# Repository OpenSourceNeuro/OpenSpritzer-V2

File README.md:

<h1 align="center"> OpenSpritzer v2</h1>
<h3 align="center">  An Open hardware pressure ejection system for reliably delivering picolitre volumes.</h3></p>
<h6 align="right">developed by M.J.Y. Zimmermann</h6>

<br></br>

This project is licensed under the <a href="https://www.gnu.org/licenses/gpl-3.0.html">GNU General Public License v3.0</a>
<br>
The hardware is licensed under the <a href="https://cern-ohl.web.cern.ch">CERN OHL v1.2</a>

***

<div align= "justify">

<p>
Designed for ease of use, robustness and low-cost, the “Openspritzer” is an open hardware “Picospritzer” as routinely used in biological labs around the world. The performance of Openspritzer and commercial alternatives is effectively indistiguishable.
</p>

<p>
The system is based on a solenoid valve connected to a pressure gauge. Control can be attained directly via an external TTL pulse or internally through an Arduino set by a rotary encoder. The basic setup can be put together for ~400€, or substantially less if you are prepare to shop around.
</p>

<p>
We anticipate that due to its high performance and low cost Openspritzer will be of interest to a broad range of researchers working in the life and physical sciences.
</p>

<br>

</div>

<p align= "right">
The original work was published in <a href="https://www.nature.com/articles/s41598-017-02301-2"> Forman et al. 2017, Scientific Reports</a>
</p>

***

<h2 align="left">
OpenSpritzer, a DIY open source micro-injector:
</h2>

<br>

<div align= "justify">

<p>
Compared to similar commercial systems that can cost up to several thousand pounds, the cost of the fully equipped Openspritzer (~£300) makes it particularly attractive for those wishing to pursue cutting-edge techniques in low resource environments.
</p>

<p>
This repository contains detailed <a href="https://github.com/OpenSourceNeuro/OpenSpritzer-V2/blob/main/Installation_Manual.md">assembly instructions and an operation manual</a> for OpenSpritzer. The <a href="https://github.com/OpenSourceNeuro/OpenSpritzer-V2/blob/main/BOM.csv">bill of material</a> details all pneumatic, mechanical and electronic components required.
</p>

<p>
To simplify the wiring assembly, a customed circuit board has been designed. PCB prototype companies (i.e. <a href="jlcpcb.com"> JLCPCB</a>) will only require the <a href="https://github.com/OpenSourceNeuro/OpenSpritzer-V2/tree/main/PCB_Rack%20version"> gerber.zip</a> folder to be sent to them for production.
</p>

<br></br>

</div>

***

<h2 align="left">
Openspritzer rivals the performance of commercial systems:
</h2>

<br>

<div align= "justify">

<p>
Openspritzer control over dose delivery matches that of a leading commercial alternative.
</p>

<p>
To directly assess the time precision and reliability of Openspritzer we visualised fluorescent dye puffs from a sharp microelectrode under two-photon microscopy. The images were taken from a puff with a duration of several seconds using a wide area scan (rectangles).
</p>

<p>
Fluorescence profiles of different command-duration puffs are shown for Openspritzer (green) and Picospritzer, a popular microinjection system(purple), respectively. The same data is shown again in log-log space to highlight details of shorter pulses. Overall, both devices behave in a very similar way in terms of providing effective and near linear control over the total dosage.
</p>

<br></br>

</div>

***

<h2 align="left">
OpenSpritzer in neuroscience experiments:
</h2>

<br>

<div align= "justify">

<p>
Openspritzer controls neural activity by delivering neurotransmitters with millisecond precision.
</p>

<p>
To demonstrate the utility of Openspritzer, we use it in a series of standard neurobiological applications: We delivered precise amounts of glutamate(cyan) and GABA(orange) to hippocampal neurons to elicit time- and dose-precise excitatory and inhibitory responses respectively, while monitoring the voltage response of the recorded neuron in current-clamp mode.
</p>

<p>
20 ms doses of glutamate (100 μM) reliably evoked excitatory postsynaptic potentials (EPSPs) and action potentials. Similarly, action potential activity elicited via somatic current injection could be suppressed by 20 ms puffs of GABA (100 μM).
</p>

<p>
To assess the accuracy of the drug delivery, we applied 10 sweeps where a 20 ms glutamate puff was applied after 500 ms produced almost identical EPSPs demonstrating the precise timing of Openspritzer and highly conserved puff volumes.
</p>

<p>
Then, to test the effect of command duration on effective dose delivey, we next applied puffs of increasing duration from 10 to 100 ms in 10 ms steps. Here, each additional 10 ms increase in duration produced a clear increase in both EPSP duration and amplitude. These results confirm the reliability and precision of Openspritzer for delivering small doses of an agent to a widely used biological sample in a controlled manner.
</p>

<br></br>

</div>

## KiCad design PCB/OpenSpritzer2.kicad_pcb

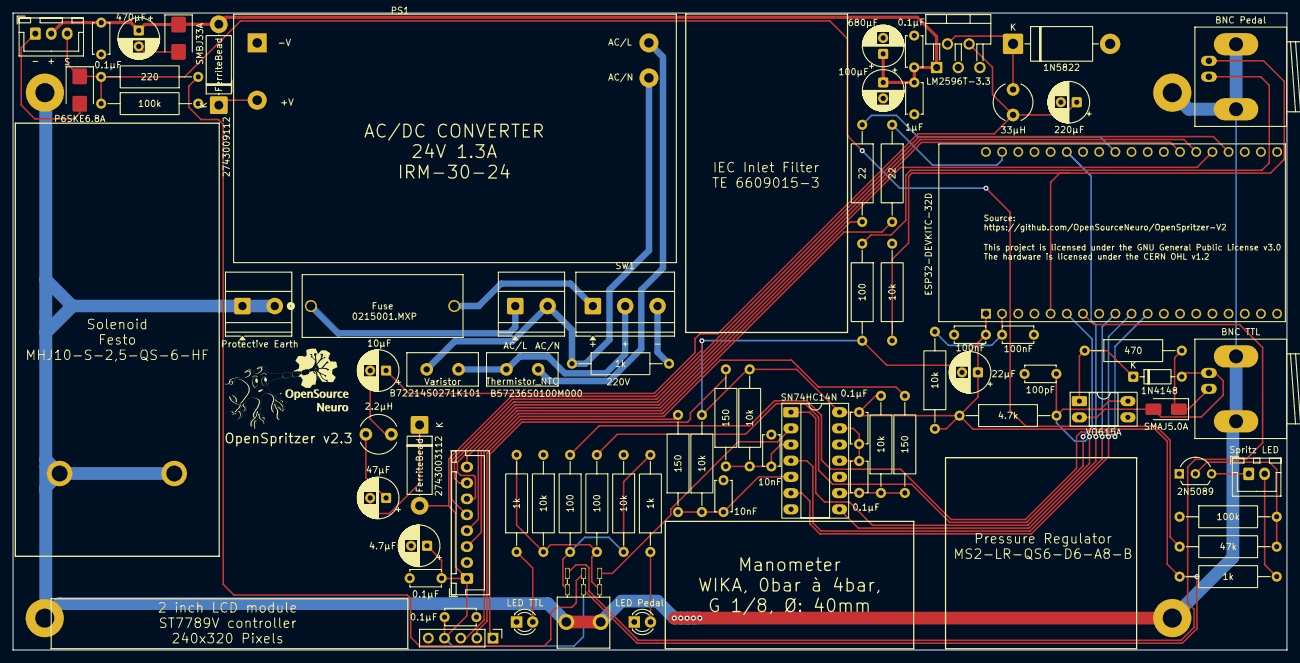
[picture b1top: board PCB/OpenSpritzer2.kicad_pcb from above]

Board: 2 copper layers, 200.0 x 100.0 mm, 79 parts (0 on the bottom side), 52 nets.

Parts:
C1: 470μF; CP_Radial_D6.3mm_P2.50mm
C2, C6, C10, C15, C17, C20: 0.1μF; C_Disc_D4.7mm_W2.5mm_P5.00mm
C3: 680μF; CP_Radial_D6.3mm_P2.50mm
C4: 100μF; CP_Radial_D6.3mm_P2.50mm
C5: 1μF; C_Disc_D4.7mm_W2.5mm_P5.00mm
C7: 220μF; CP_Radial_D6.3mm_P2.50mm
C8: 10μF; CP_Radial_D6.3mm_P2.50mm
C9: 47μF; CP_Radial_D6.3mm_P2.50mm
C11: 100pF; C_Disc_D4.7mm_W2.5mm_P5.00mm
C12: 22μF; CP_Radial_D6.3mm_P2.50mm
C13, C14: 100nF; C_Disc_D4.7mm_W2.5mm_P5.00mm
C16: 4.7μF; CP_Radial_D6.3mm_P2.50mm
C18, C19: 10nF; C_Disc_D4.7mm_W2.5mm_P5.00mm
D1: SMBJ33A; D_SMB
D2: P6SKE6.8A; D_SMB
D3: 1N5822; D_DO-201AD_P15.24mm_Horizontal
D4: SMAJ5.0A; D_SMA
D5: 1N4148; D_DO-35_SOD27_P7.62mm_Horizontal
D6: Spritz LED; JST_XH_B2B-XH-A_1x02_P2.50mm_Vertical
D7: LED Pedal; LED_D3.0mm
D8: LED TTL; LED_D3.0mm
F1: Fuse; FUSE_65600001009_LTF
FB1, FB2: FerriteBead; D_5W_P12.70mm_Horizontal
H1, H2, H3, H4: MountingHole; MountingHole_3mm
J1, J2: Screw_Terminal; TerminalBlock_Phoenix_MKDS-1,5-2-5.08_1x02_P5.08mm_Horizont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
J3: to Solenoid; JST_XH_B3B-XH-A_1x03_P2.50mm_Vertical
J4: BNC Pedal; BNC_Socket_TYCO-AMP_LargePads
J5: BNC TTL; BNC_Socket_TYCO-AMP_LargePads
L1: 33μH; L_Radial_D6.0mm_P4.00mm
L2: 2.2μH; L_Radial_D6.0mm_P4.00mm
PS1: IRM-30-24; Converter_ACDC_MeanWell_IRM-10-xx_THT
Q1: 2N5089; TO-92L_Inline_Wide
R1, R12, R20, R21: 1k; R_Axial_DIN0309_L9.0mm_D3.2mm_P15.24mm_Horizontal
R2, R11: 100k; R_Axial_DIN0309_L9.0mm_D3.2mm_P15.24mm_Horizontal
R3, R22, R23: 100; R_Axial_DIN0309_L9.0mm_D3.2mm_P15.24mm_Horizontal
R4, R7, R13, R15, R17, R24, R25: 10k; R_Axial_DIN0309_L9.0mm_D3.2mm_P15.24mm_Horizontal
R5: 470; R_Axial_DIN0309_L9.0mm_D3.2mm_P15.24mm_Horizontal
R6: 4.7k; R_Axial_DIN0309_L9.0mm_D3.2mm_P15.24mm_Horizontal
R8, R9: 22; R_Axial_DIN0309_L9.0mm_D3.2mm_P15.24mm_Horizontal
R10: 47k; R_Axial_DIN0309_L9.0mm_D3.2mm_P15.24mm_Horizontal
R14, R16, R18: 150; R_Axial_DIN0309_L9.0mm_D3.2mm_P15.24mm_Horizontal
R19: 220; R_Axial_DIN0309_L9.0mm_D3.2mm_P15.24mm_Horizontal
RV1: Varistor; C_Disc_D11.0mm_W5.0mm_P5.00mm
SW1: SW_SPST_LED; TerminalBlock_Phoenix_MKDS-1,5-3-5.08_1x03_P5.08mm_Horizont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
SW2: Rotary Encoder; PinHeader_1x05_P2.54mm_Vertical
SW3: SW_Push_DPDT; maxi_DPDT_Angled
TH1: Thermistor_NTC; C_Disc_D11.0mm_W5.0mm_P5.00mm
U1: LM2596T-3.3; TO-220-5_P3.4x3.7mm_StaggerOdd_Lead3.8mm_Vertical
U2: SN74HC14N; DIP-14_W7.62mm_Socket_LongPads
U3: VO615A; DIP-4_W7.62mm_Socket_LongPads
U4: ESP32-DEVKITC-32D; MODULE_ESP32-DEVKITC-32D
U5: ST7789V Screen; JST_XH_B8B-XH-A_1x08_P2.50mm_Vertical

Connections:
3.3V: C10.1, C12.1, C13.1, C15.2, C16.1, C17.2, FB2.2, R3.2, R6.1, R7.1, R12.2, R13.2, R15.2, R17.2, SW2.4 (S1), SW3.5 (B), U2.14 (VCC), U4.1 (3V3), U5.1 (VCC)
+3.3V: C9.2, FB2.1
+24V: C1.1, C2.1, C3.1, C4.1, C5.1, C6.1, D1.1, FB1.2, J3.2, U1.1 (VIN)
AC/L: PS1.2 (AC/L), TH1.2
AC/N: J1.2, PS1.1 (AC/N), R1.1, RV1.2
ESP_En: SW3.1 (A), U4.7 (IO32)
GNDREF: C1.2, C2.2, C3.2, C4.2, C5.2, C6.2, C7.2, C10.2, C11.2, C12.2, C13.2, C14.2, C15.1, C16.2, C17.1, C18.2, C19.2, C20.2, D1.2, D2.2, D3.2 (A), D7.1 (K), D8.1 (K), J3.1, PS1.3 (-Vo), Q1.1 (E), R2.2, R4.2, R11.1, R24.1, R25.1, SW2.5 (S2), U1.3 (GND), U1.5 (~ON/OFF), U2.7 (GND), U2.11, U2.13, U3.3, U4.14 (GND1), U4.20 (GND3), U4.26 (GND2), U5.2 (GND)
unnamed: C8.2, L2.1
unnamed: C9.1, L2.2
unnamed: C11.1, R6.2, U2.1, U3.4
unnamed: C18.1, R13.1, R14.1, U2.3
unnamed: C19.1, R15.1, R16.1, U2.5
unnamed: C20.1, R17.1, R18.1, U2.9
unnamed: D3.1 (K), L1.1, U1.2 (OUT)
unnamed: D4.1 (A1), J5.1 (In), R5.2
unnamed: D4.2 (A2), D5.2 (A), J5.2 (Ext), U3.2
unnamed: D5.1 (K), R5.1, U3.1
unnamed: D6.2 (A), R12.1
unnamed: D6.1 (K), Q1.3 (C)
unnamed: D7.2 (A), R20.1
unnamed: D8.2 (A), R21.1
unnamed: F1.2, SW1.1
unnamed: F1.1, J1.1
unnamed: J4.1 (In), R3.1
unnamed: FB1.1, PS1.4 (+Vo)
unnamed: Q1.2 (B), R10.1, R11.2
unnamed: R19.1, SW3.2 (B)
unnamed: R20.2, R22.2, R25.2, SW3.4 (A)
unnamed: R21.2, R23.2, R24.2, SW3.6 (C)
unnamed: RV1.1, SW1.2, TH1.1
unnamed: R1.2, SW1.3 (K)
unnamed: C7.1, C8.1, L1.2, U1.4 (FB)
unnamed: C14.1, R7.2, U4.2 (EN)
unnamed: R9.1, U4.28 (IO18)
unnamed: R8.1, U4.21 (IO23)
Pedal_Input: J4.2 (Ext), R4.1, U4.5 (IO34)
Pedal_Switch: R22.1, U4.11 (IO27)
RotEn_CLK: R14.2, SW2.1 (A)
RotEn_DT: R16.2, SW2.2 (C)
RotEn_SW: R18.2, SW2.3 (B)
Rot_CLK: U2.4, U4.9 (IO25)
Rot_DT: U2.6, U4.10 (IO26)
Rot_SW: U2.8, U4.25 (IO21)
Screen_BL: U4.34 (IO2), U5.8 (BL)
Screen_CLK: R9.2, U5.4 (CLK)
Screen_CS: U4.35 (IO15), U5.5 (CS)
Screen_DC: U4.32 (IO4), U5.6 (DC)
Screen_DIN: R8.2, U5.3 (DIN)
Screen_RST: U4.33 (IO0), U5.7 (RST)
Solenoid: D2.1, J3.3, R2.1, R10.2, R19.2
TTL_En: SW3.3 (C), U2.2
TTL_Switch: R23.1, U4.6 (IO35)

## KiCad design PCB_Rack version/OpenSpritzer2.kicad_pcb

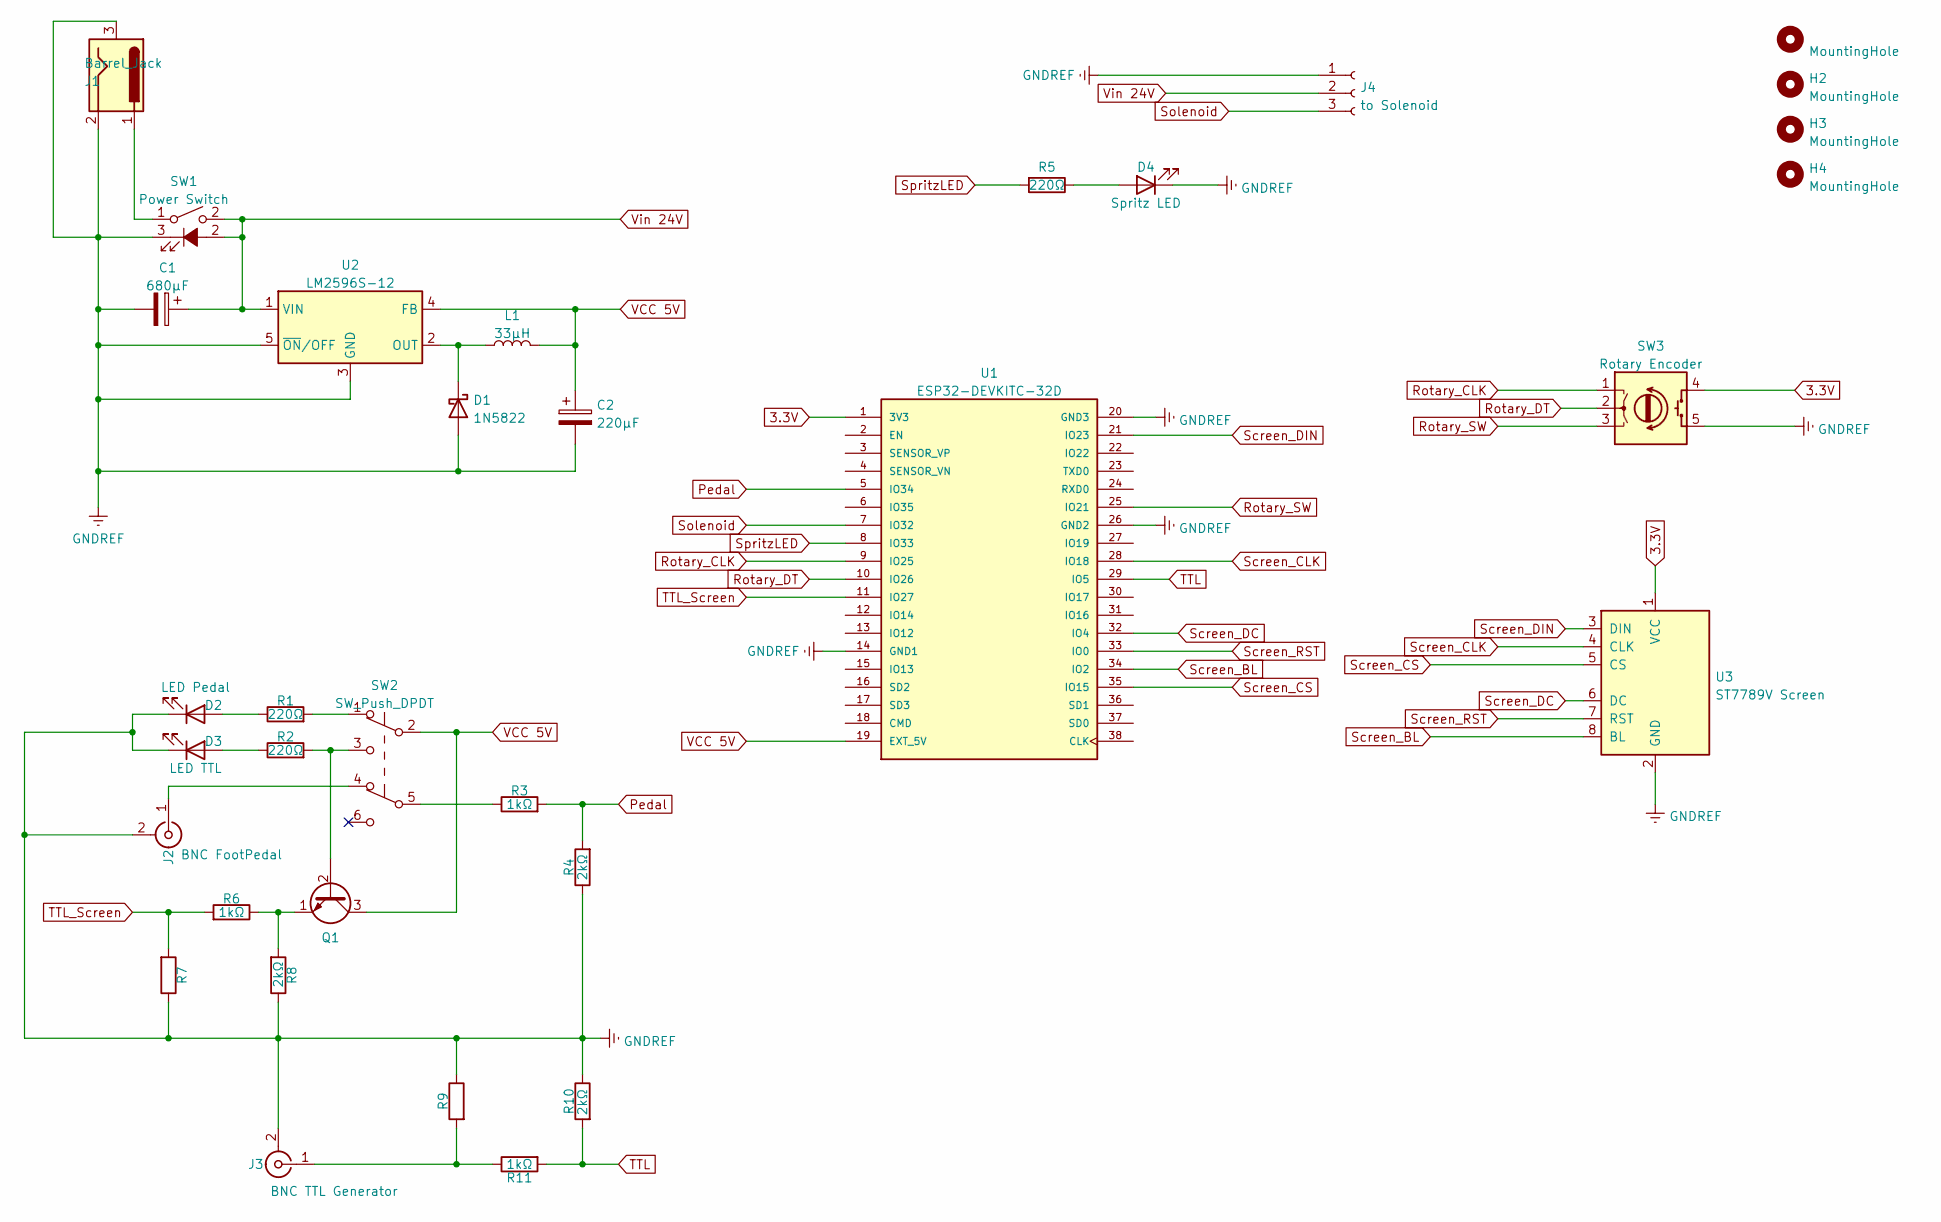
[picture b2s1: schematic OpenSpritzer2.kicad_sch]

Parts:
C1: 680μF; CP_Radial_D6.3mm_P2.50mm
C2: 220μF; CP_Radial_D6.3mm_P2.50mm
D1: 1N5822; D_DO-201AD_P15.24mm_Horizontal
D2: LED Pedal; LED_D3.0mm
D3: LED TTL; LED_D3.0mm
D4: Spritz LED; JST_XH_B2B-XH-A_1x02_P2.50mm_Vertical
H1, H2, H3, H4: MountingHole; MountingHole_3mm
J1: Barrel_Jack; BarrelJack_Horizontal
J2: BNC FootPedal; BNC_Socket_TYCO-AMP_LargePads
J3: BNC TTL Generator; BNC_Socket_TYCO-AMP_LargePads
J4: to Solenoid; JST_XH_B3B-XH-A_1x03_P2.50mm_Vertical
L1: 33μH; L_Radial_D6.0mm_P4.00mm
Q1: (no value)
R1, R2, R5: 220Ω; R_Axial_DIN0309_L9.0mm_D3.2mm_P15.24mm_Horizontal
R3, R6, R11: 1kΩ; R_Axial_DIN0309_L9.0mm_D3.2mm_P15.24mm_Horizontal
R4, R8, R10: 2kΩ; R_Axial_DIN0309_L9.0mm_D3.2mm_P15.24mm_Horizontal
R7, R9: R_Axial_DIN0309_L9.0mm_D3.2mm_P15.24mm_Horizontal
SW1: Power Switch; JST_XH_B3B-XH-A_1x03_P2.50mm_Vertical
SW2: SW_Push_DPDT; maxi_DPDT_Angled
SW3: Rotary Encoder; PinHeader_1x05_P2.54mm_Vertical
U1: ESP32-DEVKITC-32D; MODULE_ESP32-DEVKITC-32D; PARTREV 4
U2: LM2596S-12; TO-220-5_P3.4x3.7mm_StaggerOdd_Lead3.8mm_Vertical
U3: ST7789V Screen; JST_XH_B8B-XH-A_1x08_P2.50mm_Vertical

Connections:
3.3V: SW3.4 (S1), U1.1 (3V3), U3.1 (VCC)
GNDREF: C1.2, C2.2, D1.2 (A), D2.1 (K), D3.1 (K), D4.1 (K), J1.2, J1.3, J2.2 (Ext), J3.2 (Ext), J4.1, R4.1, R7.1, R8.1, R9.1, R10.1, SW1.3 (K), SW3.5 (S2), U1.14 (GND1), U1.20 (GND3), U1.26 (GND2), U2.3 (GND), U2.5 (~ON/OFF), U3.2 (GND)
unnamed: D1.1 (K), L1.1, U2.2 (OUT)
unnamed: D2.2 (A), R1.1
unnamed: D3.2 (A), R2.1
unnamed: D4.2 (A), R5.1
unnamed: J1.1, SW1.1
unnamed: J2.1 (In), SW2.4 (A)
unnamed: J3.1 (In), R9.2, R11.1
unnamed: R1.2, SW2.1 (A)
unnamed: Q1.2 (B), R2.2, SW2.3 (C)
unnamed: R3.1, SW2.5 (B)
unnamed: Q1.1 (E), R6.1, R8.2
Pedal: R3.2, R4.2, U1.5 (IO34)
Rotary_CLK: SW3.1 (A), U1.9 (IO25)
Rotary_DT: SW3.2 (C), U1.10 (IO26)
Rotary_SW: SW3.3 (B), U1.25 (IO21)
Screen_BL: U1.34 (IO2), U3.8 (BL)
Screen_CLK: U1.28 (IO18), U3.4 (CLK)
Screen_CS: U1.35 (IO15), U3.5 (CS)
Screen_DC: U1.32 (IO4), U3.6 (DC)
Screen_DIN: U1.21 (IO23), U3.3 (DIN)
Screen_RST: U1.33 (IO0), U3.7 (RST)
Solenoid: J4.3, U1.7 (IO32)
SpritzLED: R5.2, U1.8 (IO33)
TTL: R10.2, R11.2, U1.29 (IO5)
TTL_Screen: R6.2, R7.2, U1.11 (IO27)
VCC 5V: C2.1, L1.2, Q1.3 (C), SW2.2 (B), U1.19 (EXT_5V), U2.4 (FB)
Vin 24V: C1.1, J4.2, SW1.2, U2.1 (VIN)

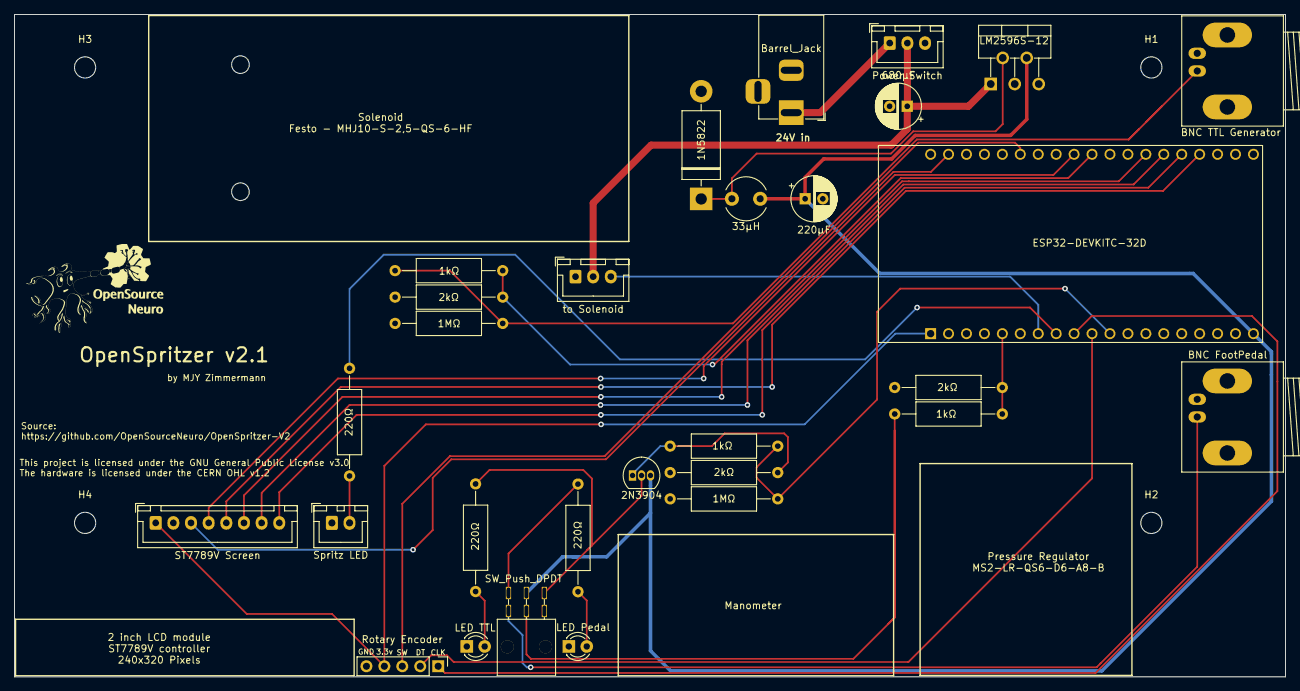
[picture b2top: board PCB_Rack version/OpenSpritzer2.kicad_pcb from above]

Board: 2 copper layers, 180.0 x 93.8 mm, 33 parts (0 on the bottom side), 29 nets.

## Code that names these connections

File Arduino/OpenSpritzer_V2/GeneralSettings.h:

#include <PNGdec.h>
#include <SPI.h>
#include <Wire.h>
#include <Adafruit_GFX.h>

#include "WelcomeScreen.h"
#include "AiEsp32RotaryEncoder.h"
#include "AiEsp32RotaryEncoderNumberSelector.h"
#include "Menus.h"

bool Flag_Menu;
bool Flag_MenuSelection;
bool Flag_TTL;

bool menu_select;
bool menu_select_close;
bool TitleFlag;

bool Switch_TTL_Flag = false;
bool TTLReading = false;
int PreviousTTLState = LOW;
bool TTL_Screen_Flag = false;

bool Switch_Pedal_Flag = false;
bool PedalReading = false;
int PreviousPedalState = LOW;

#define Solenoid      32
#define SpritzLED     33
#define Pedal         34
#define TTL            5

#define Switch_Pedal  27
#define Switch_TTL    35

#define Rotary_SW     21
#define Rotary_DT     26
#define Rotary_CLK    25
#define Rotary_VCC    -1 
#define Rotary_Steps   4

AiEsp32RotaryEncoder *rotaryEncoder = new AiEsp32RotaryEncoder(Rotary_DT, Rotary_CLK, Rotary_SW, Rotary_VCC, Rotary_Steps);
AiEsp32RotaryEncoderNumberSelector numberSelector = AiEsp32RotaryEncoderNumberSelector();

unsigned long RotaryAcceleration = 250;
int RotaryMinimum                = 0;
int RotaryMaximum                = 999999;
static unsigned long RotaryTime;
unsigned long RotaryDuration     = 10000;
void IRAM_ATTR readEncoderISR(){
    rotaryEncoder->readEncoder_ISR();
}



void HardwareSettings(){

    tft.setRotation(3);

    TitleFlag = true;

    Flag_Menu = false;
    Flag_MenuSelection = false;
    Flag_MenuSelected = false;
    Flag_TTL = true;

    menu1_selected = false;
    menu2_selected = false;
    menu3_selected = false;
    menu_select = false;
    menu_select_close = false;

    rotaryEncoder->begin();
    rotaryEncoder->setup(readEncoderISR);
    numberSelector.attachEncoder(rotaryEncoder);

    pinMode(Pedal, INPUT);
    pinMode(TTL, INPUT);

    pinMode(Solenoid, OUTPUT);
    pinMode(SpritzLED, OUTPUT);

    pinMode(Switch_Pedal, INPUT);
    pinMode(Switch_TTL, INPUT);

    digitalWrite(Solenoid, LOW); 
    digitalWrite(SpritzLED, LOW);  

    Serial.begin(115200);
}



void Menu_Loop(){

  numberSelector.setRange(0, 2, 1, true, 0);
  numberSelector.setValue(0);
  rotaryEncoder->setAcceleration(0);
  MenuSelection = 0;
  Flag_Menu = true;
  Flag_MenuSelection = true;
  FirstMenuSelected();
}


void Menu_Selection(){

  MenuSelection = numberSelector.getValue();
  
  if (MenuSelection == 0 && Flag_MenuSelected == true){
    FirstMenuSelected();
  }
  if (MenuSelection == 1 && Flag_MenuSelected == true){
    SecondMenuSelected();
  }
  if (MenuSelection == 2 && Flag_MenuSelected == true){
    ThirdMenuSelected();    
  }
}


void MenuSelection_Loop_Close(){

  if (MenuSelection == 0){
    menu1_selected = false;
    menu_select = false;
    menu_select_close = false;
    FirstMenuSelected();
    numberSelector.setRange(0, 2, 1, true, 0);
    numberSelector.setValue(MenuSelection);
    rotaryEncoder->setAcceleration(0);
  }

  if (MenuSelection == 1){
    menu2_selected = false;
    menu_select = false;
    menu_select_close = false;
    SecondMenuSelected();
    numberSelector.setRange(0, 2, 1, true, 0);
    numberSelector.setValue(MenuSelection);
    rotaryEncoder->setAcceleration(0);
  }

  if (MenuSelection == 2){
    menu3_selected = false;
    menu_select = false;
    menu_select_close = false;
    ThirdMenuSelected();
    numberSelector.setRange(0, 2, 1, true, 0);
    numberSelector.setValue(MenuSelection);
    rotaryEncoder->setAcceleration(0);
  }
}


void MenuSelection_Loop_Open(){

  if (MenuSelection == 0){
    menu1_selected = true;
    menu_select_close = true;
    FirstMenuSelectedText();
    numberSelector.setRange(1, 100, 1, false, 0);
    numberSelector.setValue(NumberOfPulse);
    rotaryEncoder->setAcceleration(0);
  }

  if (MenuSelection == 1){
    menu2_selected = true;
    menu_select_close = true;
    SecondMenuSelectedText();
    numberSelector.setRange(RotaryMinimum, RotaryMaximum, 1, false, 0);
    numberSelector.setValue(PulseOn);
    rotaryEncoder->setAcceleration(RotaryAcceleration);  
  }

  if (MenuSelection == 2){
    menu3_selected = true;
    menu_select_close = true;
    ThirdMenuSelectedText();
    
    numberSelector.setRange(RotaryMinimum, RotaryMaximum, 1, false, 0);
    numberSelector.setValue(PulseOff);
    rotaryEncoder->setAcceleration(RotaryAcceleration);  
  }

}

void NumberOfPulse_Loop(){
  NumberOfPulse = numberSelector.getValue();
  FirstMenuSelectedText();
}

void PulseOn_Loop(){
  PulseOn = numberSelector.getValue();
  SecondMenuSelectedText();
}

void PulseOff_Loop(){
  PulseOff = numberSelector.getValue();
  ThirdMenuSelectedText();
}

void Refresh(){
  RotaryTime = 0;
  Flag_Menu = false;
  PedalScreen();
}

void Pulse(){
  for (int i = 1; i <= NumberOfPulse; i++){
    digitalWrite(Solenoid, HIGH);
    digitalWrite(SpritzLED, HIGH);
    delay(PulseOn);
    digitalWrite(Solenoid, LOW);
    digitalWrite(SpritzLED, LOW);
    delay(PulseOff);
  }
}

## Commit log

2023-10-06 Upload Arduino
2023-10-06 Upload Casing
2023-10-06 Upload images
2023-10-06 Upload PCB
2023-10-24 update pcb
2024-01-01 update casing
2024-01-06 update images
2024-01-06 create Arduino libraires
2024-02-20 Re-update commit
2024-02-20 update arduino
2025-07-15 update STL
2025-07-15 update SCAD
2025-07-15 update lasercut files
2025-07-15 update DXF
